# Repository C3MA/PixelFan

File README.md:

# Projektbeschreibung
In diesem Projekt wurde ein Handelsüblicher Standventilator zum Rotationsdisplay umfunktioniert.

Details und eine Präsentation dazu gibt es hier:

[C3MA Vortrag](https://www.ccc-mannheim.de/wiki/Seminar_17._M%C3%A4rz_2023)

## Aufbau
Es gibt insgesamt 3 identische LED Leisten (PCB/LED_Leiste) mit jeweils 26 HD107S LEDs.

Die LED Leisten werden dann auf der Hauptplatine (PCB/PixelFan) bestückt.

Die Hauptplatine besteht aus 2 Controllern: 

* ein STM32G071KBTX (Software unter STM_PixelFan) für die schnelle zeitkritische Ansteuerung der LEDs und der Synchronisation zur Drehung
* ein ESP32 (Software unter ESP_PixelFan) um per W-LAN eine Verbindung zur Außenwelt herzustellen

Der Ventilator öffnet ein W-LAN (SSID: PixelFan) auf dem er eine Website (unter 192.168.4.1) anzeigt. Auf der Seite können Bilder, Smileys und Text auf den Ventilator gesendet werden.

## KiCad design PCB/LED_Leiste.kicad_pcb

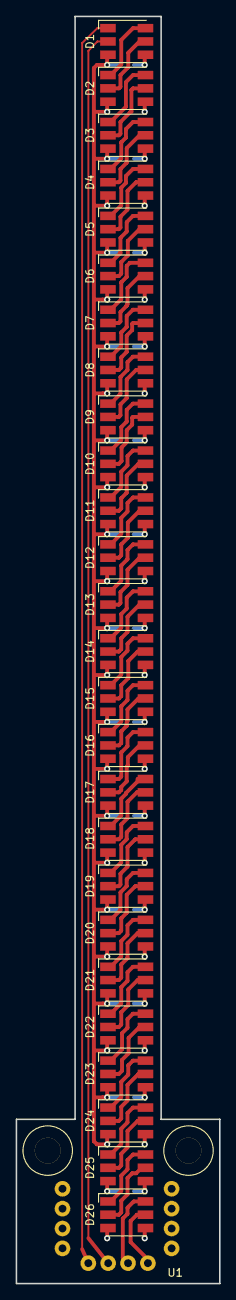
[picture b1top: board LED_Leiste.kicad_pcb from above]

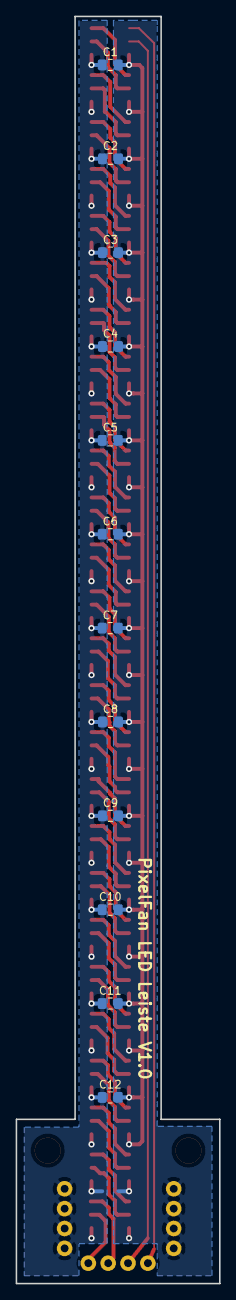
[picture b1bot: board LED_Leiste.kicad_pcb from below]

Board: 2 copper layers, 26.0 x 162.0 mm, 39 parts (12 on the bottom side), 56 nets.

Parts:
C1, C2, C3, C4, C5, C6, C7, C8, C9, C10, C11, C12: 100n; C_0805_2012Metric_Pad1.15x1.40mm_HandSolder
D1, D2, D3, D4, D5, D6, D7, D8, D9, D10, D11, D12, D13, D14, D15, D16, D17, D18, D19, D20, D21, D22, D23, D24, D25, D26: APA102; LED_RGB_5050-6
U1: Leiste; Leiste_NoOutline

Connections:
+5V: C1.1, C2.1, C3.1, C4.1, C5.1, C6.1, C7.1, C8.1, C9.1, C10.1, C11.1, C12.1, D1.4, D2.4, D3.4, D4.4, D5.4, D6.4, D7.4, D8.4, D9.4, D10.4, D11.4, D12.4, D13.4, D14.4, D15.4, D16.4, D17.4, D18.4, D19.4, D20.4, D21.4, D22.4, D23.4, D24.4, D25.4, D26.4, U1.1, U1.2, U1.3, U1.4
GND: C1.2, C2.2, C3.2, C4.2, C5.2, C6.2, C7.2, C8.2, C9.2, C10.2, C11.2, C12.2, D1.3, D2.3, D3.3, D4.3, D5.3, D6.3, D7.3, D8.3, D9.3, D10.3, D11.3, D12.3, D13.3, D14.3, D15.3, D16.3, D17.3, D18.3, D19.3, D20.3, D21.3, D22.3, D23.3, D24.3, D25.3, D26.3, U1.9, U1.10, U1.11, U1.12
unnamed: D1.1, U1.5
unnamed: D1.2, U1.6
unnamed: D1.5, D2.2
unnamed: D1.6, D2.1
unnamed: D2.5, D3.2
unnamed: D2.6, D3.1
unnamed: D3.5, D4.2
unnamed: D3.6, D4.1
unnamed: D4.5, D5.2
unnamed: D4.6, D5.1
unnamed: D5.5, D6.2
unnamed: D5.6, D6.1
unnamed: D6.5, D7.2
unnamed: D6.6, D7.1
unnamed: D7.5, D8.2
unnamed: D7.6, D8.1
unnamed: D8.5, D9.2
unnamed: D8.6, D9.1
unnamed: D9.6, D10.1
unnamed: D9.5, D10.2
unnamed: D10.5, D11.2
unnamed: D10.6, D11.1
unnamed: D11.5, D12.2
unnamed: D11.6, D12.1
unnamed: D12.5, D13.2
unnamed: D12.6, D13.1
unnamed: D13.5, D14.2
unnamed: D13.6, D14.1
unnamed: D14.5, D15.2
unnamed: D14.6, D15.1
unnamed: D15.5, D16.2
unnamed: D15.6, D16.1
unnamed: D16.5, D17.2
unnamed: D16.6, D17.1
unnamed: D17.5, D18.2
unnamed: D17.6, D18.1
unnamed: D18.5, D19.2
unnamed: D18.6, D19.1
unnamed: D19.5, D20.2
unnamed: D19.6, D20.1
unnamed: D20.5, D21.2
unnamed: D20.6, D21.1
unnamed: D21.5, D22.2
unnamed: D21.6, D22.1
unnamed: D22.5, D23.2
unnamed: D22.6, D23.1
unnamed: D23.5, D24.2
unnamed: D23.6, D24.1
unnamed: D24.5, D25.2
unnamed: D24.6, D25.1
unnamed: D25.5, D26.2
unnamed: D25.6, D26.1
unnamed: D26.5, U1.8
unnamed: D26.6, U1.7

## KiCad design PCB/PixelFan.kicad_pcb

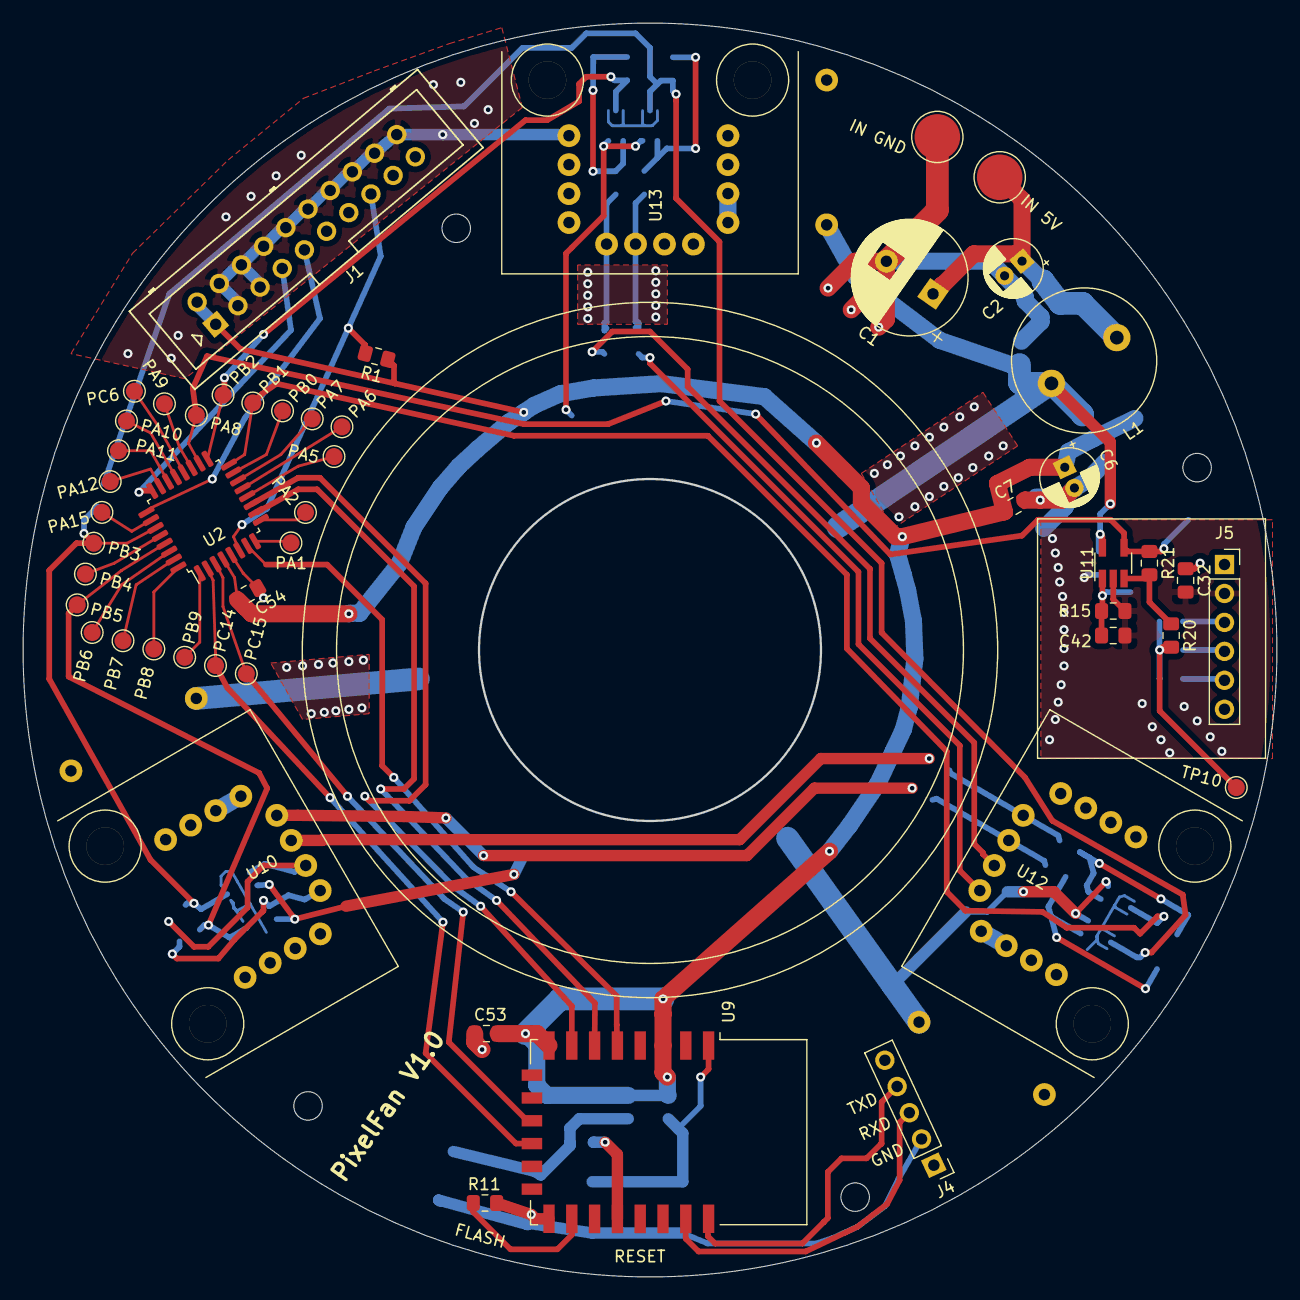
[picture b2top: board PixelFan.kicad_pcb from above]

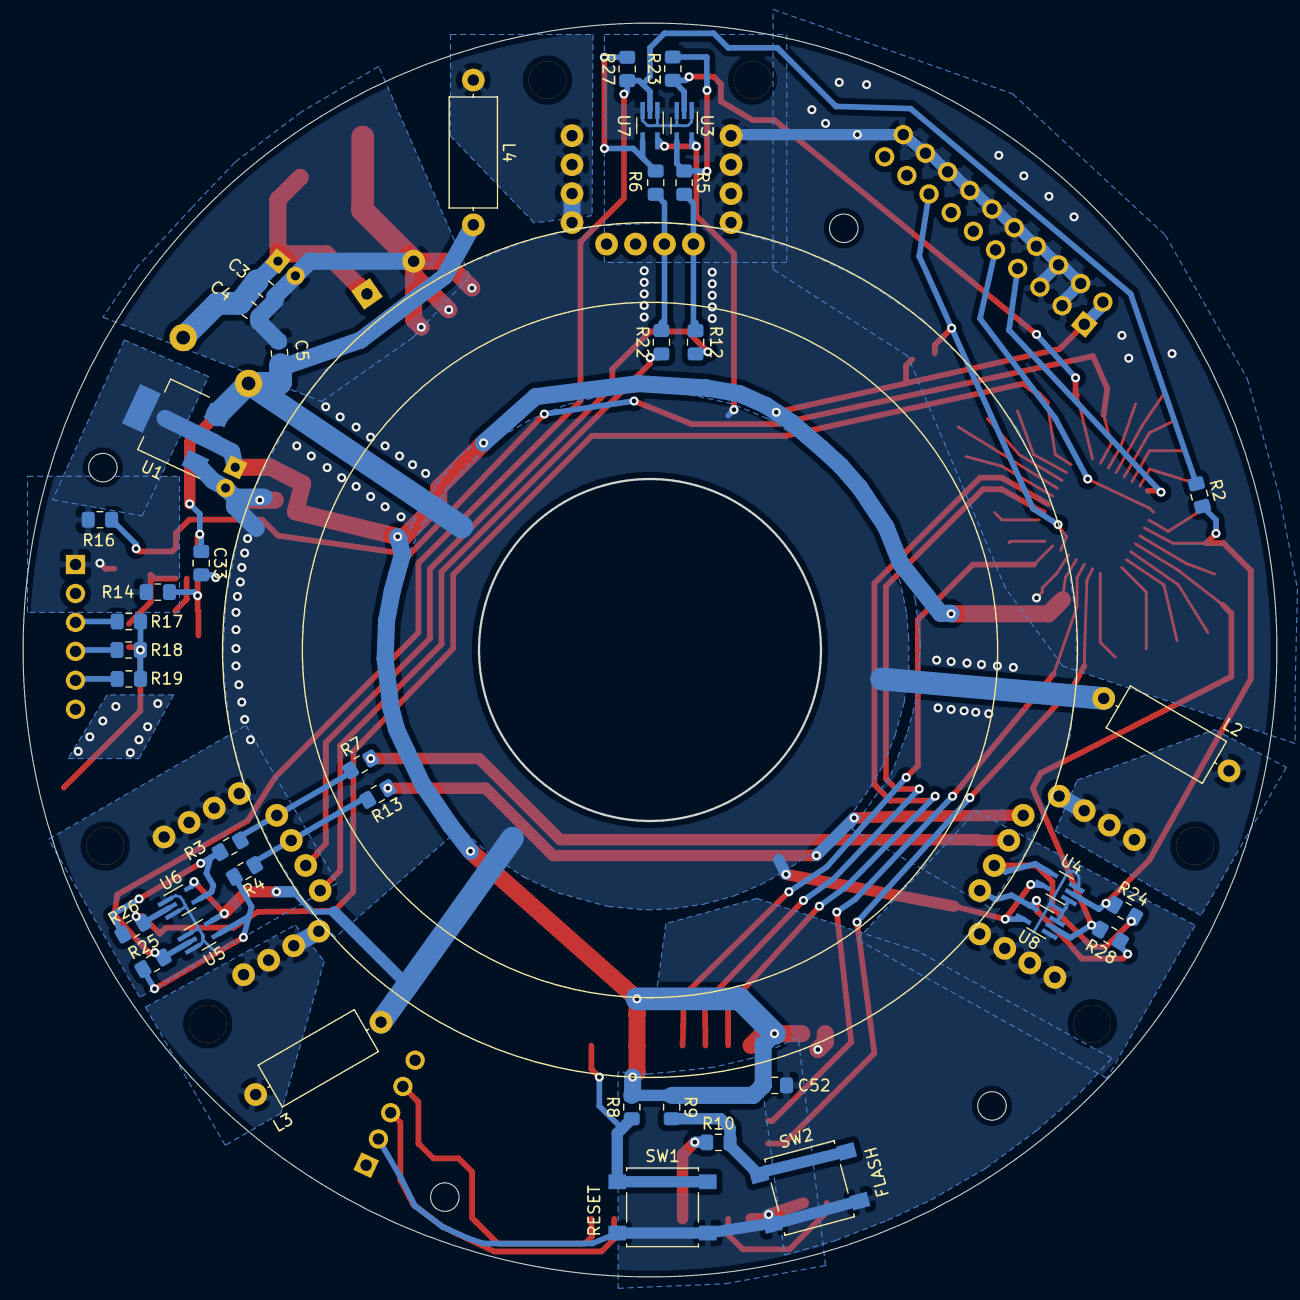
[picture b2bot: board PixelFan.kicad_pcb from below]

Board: 2 copper layers, 110.0 x 110.0 mm, 94 parts (40 on the bottom side), 64 nets.

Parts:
C1: 470µF; CP_Radial_D10.0mm_P5.00mm
C2, C6: 10u; CP_Radial_D5.0mm_P2.00mm
C3, C5, C7, C53: 470n; C_0805_2012Metric_Pad1.15x1.40mm_HandSolder
C4, C52: 10n; C_0805_2012Metric_Pad1.15x1.40mm_HandSolder
C32, C33, C42, C54: 100n; C_0805_2012Metric_Pad1.15x1.40mm_HandSolder
H1, H2, H3, H4: MountingHole; MountingHole_2.5mm
J1: Conn_02x10_Odd_Even; Multicomp_MC9A12-2034_2x10_P2.54mm_Vertical
J4: Conn_01x05_Male; PinHeader_1x05_P2.54mm_Vertical
J5: Conn_01x06_Male; PinSocket_1x06_P2.54mm_Vertical
L1: 47µH; L_Radial_D12.5mm_P7.00mm_Fastron_09HCP
L2, L3, L4: L; L_Axial_L9.5mm_D4.0mm_P12.70mm_Horizontal_Fastron_SMCC
PA1, PA2, PA5, PA6, PA7, PA8, PA9, PA10, PA11, PA12, PA15: TestPoint; TestPoint_Pad_D1.5mm
PB0, PB1, PB2, PB3, PB4, PB5, PB6, PB7, PB8, PB9: TestPoint; TestPoint_Pad_D1.5mm
PC6, PC14, PC15: TestPoint; TestPoint_Pad_D1.5mm
R1, R8, R10, R14, R16: 10k; R_0805_2012Metric_Pad1.15x1.40mm_HandSolder
R2, R3, R4, R5, R6, R7, R12, R13, R17, R18, R19, R22, R23, R24, R25, R26, R27, R28: 0; R_0805_2012Metric_Pad1.15x1.40mm_HandSolder
R9, R20: 1k; R_0805_2012Metric_Pad1.15x1.40mm_HandSolder
R11: 2k2; R_0805_2012Metric_Pad1.15x1.40mm_HandSolder
R15: 6k2; R_0805_2012Metric_Pad1.15x1.40mm_HandSolder
R21: 100k; R_0805_2012Metric_Pad1.15x1.40mm_HandSolder
SW1: Reset; SW_SPST_B3S-1000
SW2: Flash; SW_SPST_B3S-1000
TP1, TP2: TestPoint; TestPoint_Pad_D4.0mm
TP10: TestPoint; TestPoint_Pad_D1.5mm
U1: NCP1117-3.3_SOT223; SOT-223-3_TabPin2
U2: STM32G070KxTx; LQFP-32_7x7mm_P0.8mm
U3, U4, U5, U6, U7, U8: 74HCT1G125GW; SOT-353_SC-70-5_Handsoldering
U9: ESP-12F; ESP-12E
U10, U12, U13: Leiste; Leiste_WithOutline
U11: LM397; SOT-23-5_HandSoldering

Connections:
+3V3: C6.1, C7.1, C32.1, C52.1, C53.1, C54.2, J1.1, J1.2, J5.1, R1.1, R8.2, R9.1, R14.1, R16.1, U1.2, U2.4, U9.3, U9.8
+5V: C5.1, C33.1, L1.2, L2.2, L3.2, L4.2, U1.3, U3.5, U4.5, U5.5, U6.5, U7.5, U8.5, U11.5
+5VD: C1.1, C2.1, C3.1, C4.1, L1.1, TP1.1
/Beschleunigungssensor/COMP_OUT: PA8.1, R16.2, R21.1, U2.18, U11.4
/ESP8266/ESP_IO1: PC14.1, U2.2, U9.12
/ESP8266/ESP_IO2: PC15.1, U2.3, U9.11
/ESP8266/MISO: U2.10, U9.6
/ESP8266/MOSI: U2.11, U9.7
/ESP8266/SCLK: U2.7, U9.5
GND: C1.2, C2.2, C3.2, C4.2, C5.2, C6.2, C7.2, C32.2, C33.2, C42.2, C52.2, C53.2, C54.1, J1.3, J1.4, J1.5, J1.6, J1.8, J1.10, J1.12, J1.14, J1.16, J1.18, J1.20, J4.2, J5.2, R11.1, R15.2, SW1.2, SW2.2, TP2.1, U1.1, U2.5, U3.1, U3.3, U4.1, U4.3, U5.1, U5.3, U6.1, U6.3, U7.1, U7.3, U8.1, U8.3, U9.15, U10.9, U10.10, U10.11, U10.12, U11.2, U12.9, U12.10, U12.11, U12.12, U13.9, U13.10, U13.11, U13.12
unnamed: C42.1, R14.2, R15.1, U11.1
unnamed: J1.7, U2.24
unnamed: J1.9, U2.25
unnamed: J1.15, R1.2, U2.6
unnamed: J4.3, U9.21
unnamed: J4.4, U9.22
unnamed: J5.3, R17.2
unnamed: J5.4, R18.2
unnamed: J5.5, R19.2
unnamed: L2.1, U10.1, U10.2, U10.3, U10.4
unnamed: L3.1, U12.1, U12.2, U12.3, U12.4
unnamed: L4.1, U13.1, U13.2, U13.3, U13.4
unnamed: PA1.1, U2.8
unnamed: PA2.1, U2.9
unnamed: PA5.1, U2.12
unnamed: PA6.1, U2.13
unnamed: PA7.1, U2.14
unnamed: PA9.1, U2.19
unnamed: PA10.1, U2.21
unnamed: PA11.1, U2.22
unnamed: PA12.1, U2.23
unnamed: PA15.1, U2.26
unnamed: PB0.1, U2.15
unnamed: PB1.1, R26.2, U2.16, U6.2
unnamed: PB2.1, R23.1, U2.17, U3.2
unnamed: PB3.1, R2.2, R24.2, U2.27, U4.2
unnamed: PB4.1, U2.28
unnamed: PB5.1, R28.2, U2.29, U8.2
unnamed: PB6.1, U2.30
unnamed: PB7.1, U2.31
unnamed: PB8.1, U2.32
unnamed: PB9.1, U2.1
unnamed: PC6.1, U2.20
unnamed: R2.1, R25.2, R27.1, U5.2, U7.2
unnamed: R3.1, R7.2, U12.5
unnamed: R7.1, U10.7
unnamed: R8.1, SW1.1, U9.1
unnamed: R10.1, U9.18
unnamed: R9.2, R10.2, SW2.1
unnamed: R11.2, U9.16
unnamed: R12.1, U12.7
unnamed: R5.2, R12.2, U13.5
unnamed: R13.1, U10.8
unnamed: R4.1, R13.2, U12.6
unnamed: R17.1, R18.1, R19.1, R20.2, TP10.1
unnamed: R20.1, R21.2, U11.3
unnamed: R22.1, U12.8
unnamed: R6.2, R22.2, U13.6
unnamed: R5.1, R23.2, U3.4
unnamed: R24.1, U4.4, U10.6
unnamed: R4.2, R25.1, U5.4
unnamed: R3.2, R26.1, U6.4
unnamed: R6.1, R27.2, U7.4
unnamed: R28.1, U8.4, U10.5

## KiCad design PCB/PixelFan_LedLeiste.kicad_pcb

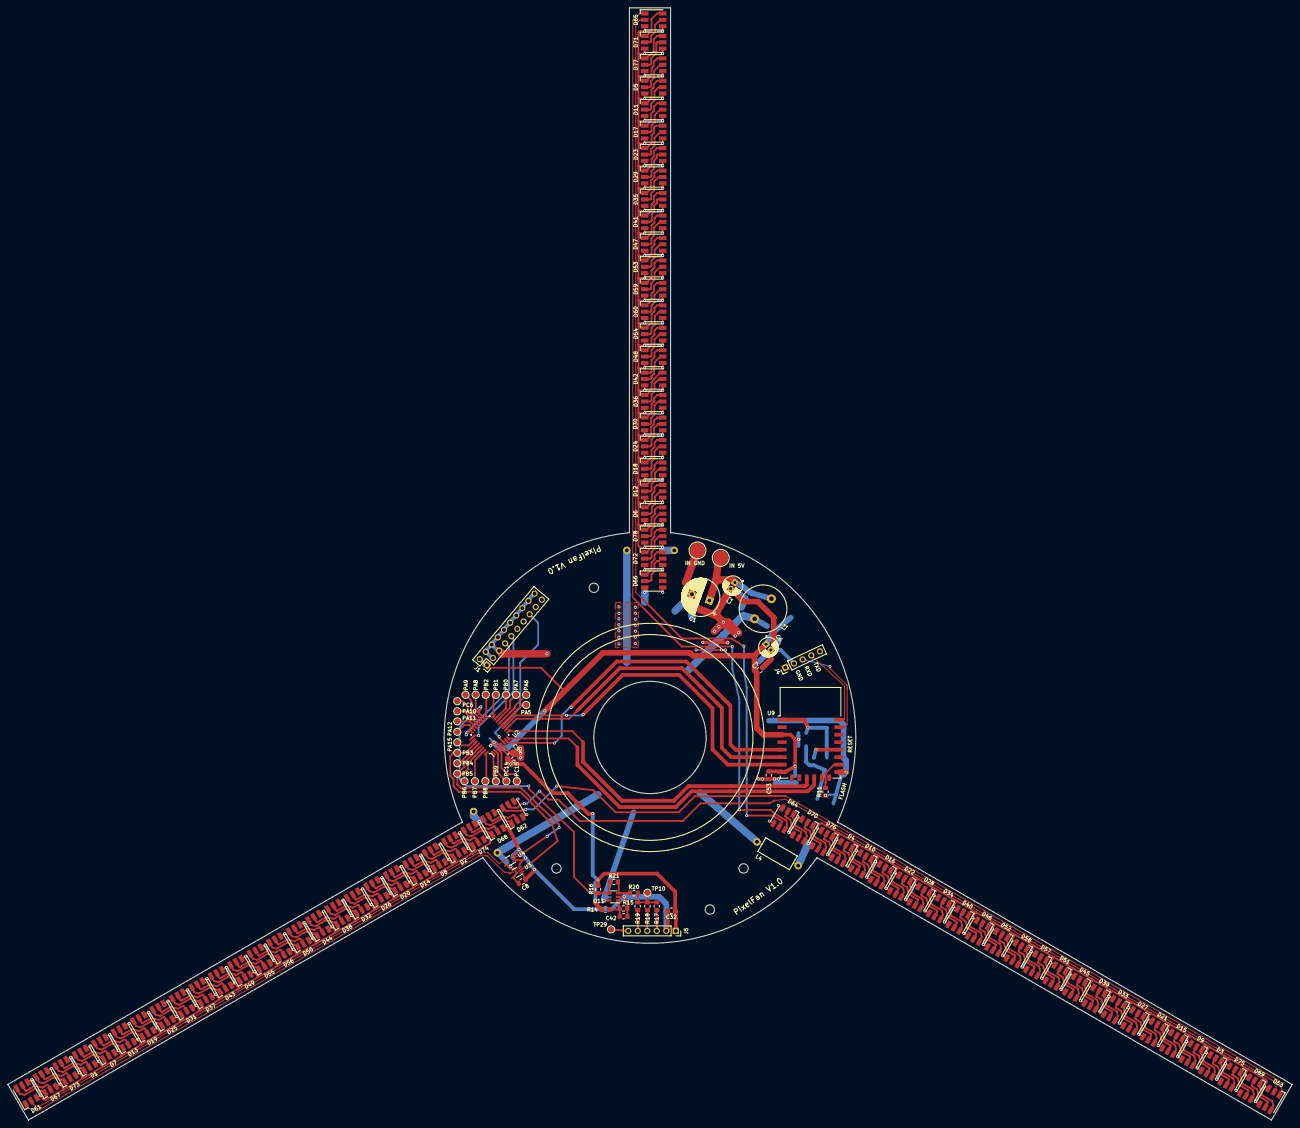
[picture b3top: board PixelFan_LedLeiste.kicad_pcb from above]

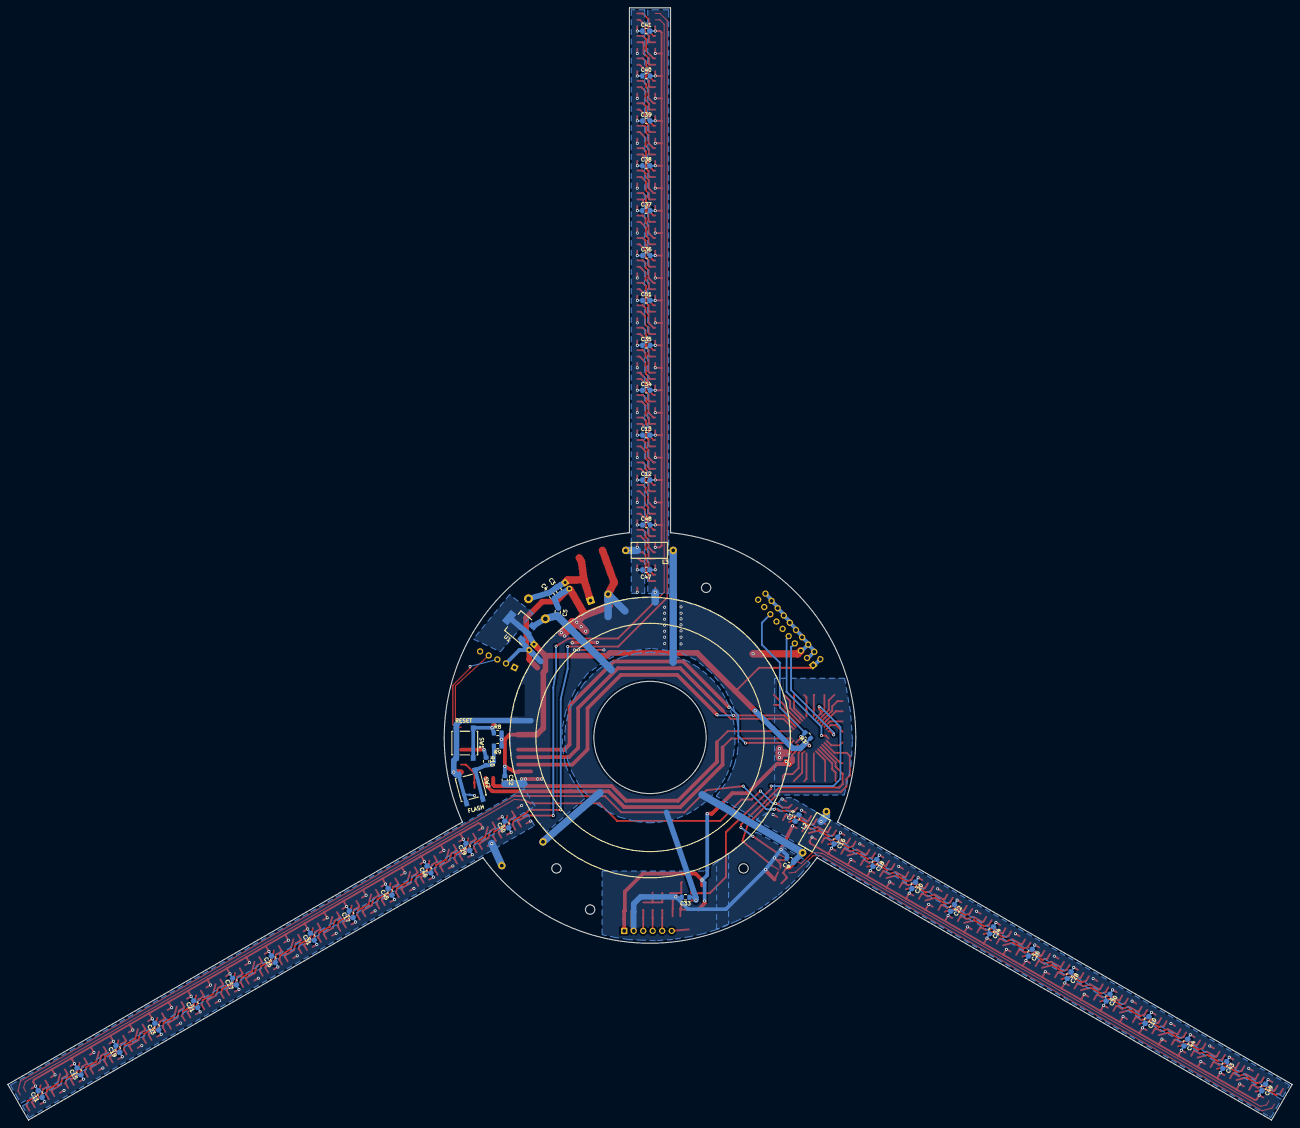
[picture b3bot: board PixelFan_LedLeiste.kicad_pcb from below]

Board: 2 copper layers, 343.2 x 297.3 mm, 190 parts (54 on the bottom side), 206 nets.

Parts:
C1: 470µF; CP_Radial_D10.0mm_P5.00mm
C2, C6: 10u; CP_Radial_D5.0mm_P2.00mm
C3, C5, C7, C53: 470n; C_0805_2012Metric_Pad1.15x1.40mm_HandSolder
C4, C52: 10n; C_0805_2012Metric_Pad1.15x1.40mm_HandSolder
C8, C9, C10, C11, C12, C13, C14, C15, C16, C17, C18, C19, C20, C21, C22, C23, C24, C25, C26, C27, C28, C29, C30, C31, C32, C33, C34, C35, C36, C37, C38, C39, C40, C41, C42, C43, C44, C45, C46, C47, C48, C49, C50, C51, C54: 100n; C_0805_2012Metric_Pad1.15x1.40mm_HandSolder
D1, D2, D3, D4, D5, D6, D7, D8, D9, D10, D11, D12, D13, D14, D15, D16, D17, D18, D19, D20, D21, D22, D23, D24, D25, D26, D27, D28, D29, D30, D31, D32, D33, D34, D35, D36, D37, D38, D39, D40, D41, D42, D43, D44, D45, D46, D47, D48, D49, D50, D51, D52, D53, D54, D55, D56, D57, D58, D59, D60, D61, D62, D63, D64, D65, D66, D67, D68, D69, D70, D71, D72, D73, D74, D75, D76, D77, D78: APA102; LED_RGB_5050-6
H1, H2, H3, H4: MountingHole; MountingHole_2.5mm
J1: Conn_02x10_Odd_Even; PinHeader_2x10_P2.54mm_Vertical
J4: Conn_01x05_Male; PinHeader_1x05_P2.54mm_Vertical
J5: Conn_01x06_Male; PinSocket_1x06_P2.54mm_Vertical
L1: 47µH; L_Radial_D12.5mm_P7.00mm_Fastron_09HCP
L2, L3, L4: 1u; L_Axial_L9.5mm_D4.0mm_P12.70mm_Horizontal_Fastron_SMCC
PA5, PA6, PA7, PA8, PA9, PA10, PA11, PA12, PA15: TestPoint; TestPoint_Pad_D1.5mm
PB0, PB1, PB2, PB3, PB4, PB5, PB6, PB7, PB8, PB9: TestPoint; TestPoint_Pad_D1.5mm
PC6, PC14, PC15: TestPoint; TestPoint_Pad_D1.5mm
R1, R8, R10, R14, R15, R16: 10k; R_0805_2012Metric_Pad1.15x1.40mm_HandSolder
R9, R20: 1k; R_0805_2012Metric_Pad1.15x1.40mm_HandSolder
R11: 2k2; R_0805_2012Metric_Pad1.15x1.40mm_HandSolder
R17, R18, R19: 0; R_0805_2012Metric_Pad1.15x1.40mm_HandSolder
R21: 100k; R_0805_2012Metric_Pad1.15x1.40mm_HandSolder
SW1: Reset; SW_SPST_B3S-1000
SW2: Flash; SW_SPST_B3S-1000
TP1, TP2: TestPoint; TestPoint_Pad_D4.0mm
TP10, TP29: TestPoint; TestPoint_Pad_D1.5mm
U1: NCP1117-3.3_SOT223; SOT-223-3_TabPin2
U2: STM32G070KxTx; LQFP-32_7x7mm_P0.8mm
U3, U4: 74HCT1G125GW; SOT-353_SC-70-5_Handsoldering
U9: ESP-12F; ESP-12E
U11: LM397; SOT-23-5_HandSoldering

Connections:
+3V3: C6.1, C7.1, C32.1, C52.1, C53.1, C54.2, J1.1, J1.2, J5.1, R1.1, R8.2, R9.1, R14.1, R16.1, U1.2, U2.4, U9.3, U9.8
+5V: C5.1, C8.1, C9.2, C33.1, L1.2, L2.1, L3.1, L4.1, U1.3, U3.5, U4.5, U11.5
+5VD: C1.1, C2.1, C3.1, C4.1, L1.1, TP1.1
/Beschleunigungssensor/COMP_OUT: PA8.1, R16.2, R21.1, U2.18, U11.4
/ESP8266/ESP_IO1: U2.8, U9.12
/ESP8266/ESP_IO2: U2.9, U9.11
/ESP8266/MISO: U2.10, U9.6
/ESP8266/MOSI: U2.11, U9.7
/ESP8266/SCLK: U2.7, U9.5
/LEDs/CLK: PB3.1, U2.27, U3.2
/LEDs/DATA: PB5.1, U2.29, U4.2
/LEDs/VCC_LINE1: C10.1, C14.1, C16.1, C18.1, C20.1, C22.1, C24.1, C26.1, C28.1, C30.1, C43.1, C44.1, C49.1, D1.4, D2.4, D7.4, D8.4, D13.4, D14.4, D19.4, D20.4, D25.4, D26.4, D31.4, D32.4, D37.4, D38.4, D43.4, D44.4, D49.4, D50.4, D55.4, D56.4, D61.4, D62.4, D67.4, D68.4, D73.4, D74.4, L2.2
/LEDs/VCC_LINE2: C11.1, C15.1, C17.1, C19.1, C21.1, C23.1, C25.1, C27.1, C29.1, C31.1, C45.1, C46.1, C50.1, D3.4, D4.4, D9.4, D10.4, D15.4, D16.4, D21.4, D22.4, D27.4, D28.4, D33.4, D34.4, D39.4, D40.4, D45.4, D46.4, D51.4, D52.4, D57.4, D58.4, D63.4, D64.4, D69.4, D70.4, D75.4, D76.4, L4.2
/LEDs/VCC_LINE3: C12.1, C13.1, C34.1, C35.1, C36.1, C37.1, C38.1, C39.1, C40.1, C41.1, C47.1, C48.1, C51.1, D5.4, D6.4, D11.4, D12.4, D17.4, D18.4, D23.4, D24.4, D29.4, D30.4, D35.4, D36.4, D41.4, D42.4, D47.4, D48.4, D53.4, D54.4, D59.4, D60.4, D65.4, D66.4, D71.4, D72.4, D77.4, D78.4, L3.2
GND: C1.2, C2.2, C3.2, C4.2, C5.2, C6.2, C7.2, C8.2, C9.1, C10.2, C11.2, C12.2, C13.2, C14.2, C15.2, C16.2, C17.2, C18.2, C19.2, C20.2, C21.2, C22.2, C23.2, C24.2, C25.2, C26.2, C27.2, C28.2, C29.2, C30.2, C31.2, C32.2, C33.2, C34.2, C35.2, C36.2, C37.2, C38.2, C39.2, C40.2, C41.2, C42.2, C43.2, C44.2, C45.2, C46.2, C47.2, C48.2, C49.2, C50.2, C51.2, C52.2, C53.2, C54.1, D1.3, D2.3, D3.3, D4.3, D5.3, D6.3, D7.3, D8.3, D9.3, D10.3, D11.3, D12.3, D13.3, D14.3, D15.3, D16.3, D17.3, D18.3, D19.3, D20.3, D21.3, D22.3, D23.3, D24.3, D25.3, D26.3, D27.3, D28.3, D29.3, D30.3, D31.3, D32.3, D33.3, D34.3, D35.3, D36.3, D37.3, D38.3, D39.3, D40.3, D41.3, D42.3, D43.3, D44.3, D45.3, D46.3, D47.3, D48.3, D49.3, D50.3, D51.3, D52.3, D53.3, D54.3, D55.3, D56.3, D57.3, D58.3, D59.3, D60.3, D61.3, D62.3, D63.3, D64.3, D65.3, D66.3, D67.3, D68.3, D69.3, D70.3, D71.3, D72.3, D73.3, D74.3, D75.3, D76.3, D77.3, D78.3, J1.3, J1.4, J1.5, J1.6, J1.8, J1.10, J1.12, J1.14, J1.16, J1.18, J1.20, J4.2, J5.2, R11.1, R15.2, SW1.2, SW2.2, TP2.1, U1.1, U2.5, U3.1, U3.3, U4.1, U4.3, U9.15, U11.2
unnamed: C42.1, R14.2, R15.1, U11.1
unnamed: D1.1, D73.6
unnamed: D1.2, D73.5
unnamed: D1.5, D7.2
unnamed: D1.6, D7.1
unnamed: D2.1, D8.6
unnamed: D2.2, D8.5
unnamed: D2.5, D74.2
unnamed: D2.6, D74.1
unnamed: D3.1, D75.6
unnamed: D3.2, D75.5
unnamed: D3.5, D9.2
unnamed: D3.6, D9.1
unnamed: D4.5, D76.2
unnamed: D4.6, D76.1
unnamed: D5.1, D77.6
unnamed: D5.2, D77.5
unnamed: D6.5, D78.2
unnamed: D6.6, D78.1
unnamed: D10.1, D16.6
unnamed: D10.2, D16.5
unnamed: D4.2, D10.5
unnamed: D4.1, D10.6
unnamed: D5.6, D11.1
unnamed: D5.5, D11.2
unnamed: D11.5, D17.2
unnamed: D11.6, D17.1
unnamed: D12.1, D18.6
unnamed: D12.2, D18.5
unnamed: D6.2, D12.5
unnamed: D6.1, D12.6
unnamed: D7.6, D13.1
unnamed: D7.5, D13.2
unnamed: D13.5, D19.2
unnamed: D13.6, D19.1
unnamed: D14.1, D20.6
unnamed: D14.2, D20.5
unnamed: D8.2, D14.5
unnamed: D8.1, D14.6
unnamed: D9.6, D15.1
unnamed: D9.5, D15.2
unnamed: D15.5, D21.2
unnamed: D15.6, D21.1
unnamed: D16.1, D22.6
unnamed: D16.2, D22.5
unnamed: D17.5, D23.2
unnamed: D17.6, D23.1
unnamed: D18.1, D24.6
unnamed: D18.2, D24.5
unnamed: D19.5, D25.2
unnamed: D19.6, D25.1
unnamed: D20.1, D26.6
unnamed: D20.2, D26.5
unnamed: D21.5, D27.2
unnamed: D21.6, D27.1
unnamed: D22.1, D28.6
unnamed: D22.2, D28.5
unnamed: D23.5, D29.2
unnamed: D23.6, D29.1
unnamed: D24.1, D30.6
unnamed: D24.2, D30.5
unnamed: D25.5, D31.2
unnamed: D25.6, D31.1
unnamed: D26.1, D32.6
unnamed: D26.2, D32.5
unnamed: D27.5, D33.2
unnamed: D27.6, D33.1
unnamed: D28.1, D34.6
unnamed: D28.2, D34.5
unnamed: D29.5, D35.2
unnamed: D29.6, D35.1
unnamed: D30.1, D36.6
unnamed: D30.2, D36.5
unnamed: D31.5, D37.2
unnamed: D31.6, D37.1
unnamed: D32.1, D38.6
unnamed: D32.2, D38.5
unnamed: D33.5, D39.2
unnamed: D33.6, D39.1
unnamed: D34.1, D40.6
unnamed: D34.2, D40.5
unnamed: D35.5, D41.2
unnamed: D35.6, D41.1
unnamed: D36.1, D42.6
unnamed: D36.2, D42.5
unnamed: D37.5, D43.2
unnamed: D37.6, D43.1
unnamed: D38.1, D44.6
unnamed: D38.2, D44.5
unnamed: D39.5, D45.2
unnamed: D39.6, D45.1
unnamed: D40.1, D46.6
unnamed: D40.2, D46.5
unnamed: D41.5, D47.2
unnamed: D41.6, D47.1
unnamed: D42.1, D48.6
unnamed: D42.2, D48.5
unnamed: D43.5, D49.2
unnamed: D43.6, D49.1
unnamed: D44.1, D50.6
unnamed: D44.2, D50.5
unnamed: D45.5, D51.2
unnamed: D45.6, D51.1
unnamed: D46.1, D52.6
unnamed: D46.2, D52.5
unnamed: D47.5, D53.2
unnamed: D47.6, D53.1
unnamed: D48.1, D54.6
unnamed: D48.2, D54.5
unnamed: D49.5, D55.2
unnamed: D49.6, D55.1
unnamed: D50.1, D56.6
unnamed: D50.2, D56.5
unnamed: D51.5, D57.2
unnamed: D51.6, D57.1
unnamed: D52.1, D58.6
unnamed: D52.2, D58.5
unnamed: D53.5, D59.2
unnamed: D53.6, D59.1
unnamed: D54.1, D60.6
unnamed: D54.2, D60.5
unnamed: D55.5, D56.2
unnamed: D55.6, D56.1
unnamed: D57.5, D58.2
unnamed: D57.6, D58.1
unnamed: D59.5, D60.2
unnamed: D59.6, D60.1
unnamed: D61.1, U3.4
unnamed: D61.2, U4.4
unnamed: D61.5, D67.2
unnamed: D61.6, D67.1
unnamed: D62.1, D68.6
unnamed: D62.2, D68.5
unnamed: D62.5, D63.2
unnamed: D62.6, D63.1
unnamed: D63.5, D69.2
unnamed: D63.6, D69.1
unnamed: D64.1, D70.6
unnamed: D64.2, D70.5
unnamed: D64.5, D65.2
unnamed: D64.6, D65.1
unnamed: D65.5, D71.2
unnamed: D65.6, D71.1
unnamed: D66.1, D72.6
unnamed: D66.2, D72.5
unnamed: D67.5, D73.2
unnamed: D67.6, D73.1
unnamed: D68.1, D74.6
unnamed: D68.2, D74.5
unnamed: D69.5, D75.2
unnamed: D69.6, D75.1
unnamed: D70.1, D76.6
unnamed: D70.2, D76.5
unnamed: D71.5, D77.2
unnamed: D71.6, D77.1
unnamed: D72.1, D78.6
unnamed: D72.2, D78.5
unnamed: J1.7, U2.24
unnamed: J1.9, U2.25
unnamed: J1.15, R1.2, U2.6
unnamed: J4.3, U9.21
unnamed: J4.4, U9.22
unnamed: J5.3, R17.2
unnamed: J5.4, R18.2
unnamed: J5.5, R19.2
unnamed: J5.6, TP29.1
unnamed: PA5.1, U2.12
unnamed: PA6.1, U2.13
unnamed: PA7.1, U2.14
unnamed: PA9.1, U2.19
unnamed: PA10.1, U2.21
unnamed: PA11.1, U2.22
unnamed: PA12.1, U2.23
unnamed: PA15.1, U2.26
unnamed: PB0.1, U2.15
unnamed: PB1.1, U2.16
unnamed: PB2.1, U2.17
unnamed: PB4.1, U2.28
unnamed: PB6.1, U2.30
unnamed: PB7.1, U2.31
unnamed: PB8.1, U2.32
unnamed: PB9.1, U2.1
unnamed: PC6.1, U2.20
unnamed: PC14.1, U2.2
unnamed: PC15.1, U2.3
unnamed: R8.1, SW1.1, U9.1
unnamed: R10.1, U9.18
unnamed: R9.2, R10.2, SW2.1
unnamed: R11.2, U9.16
unnamed: R17.1, R18.1, R19.1, R20.2, TP10.1
unnamed: R20.1, R21.2, U11.3

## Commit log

2023-01-25 First check in
2023-01-25 First checkin
2023-01-26 arduino install script for action
2023-01-26 ESP core install script for action
2023-01-26 Arduino Build with ESP core
2023-01-26 Platform source-path ergänzt
2023-01-26 WebSocketServer Bibliothek ergänzt
2023-01-26 Library name korrigiert
2023-01-26 Update README.md
    Statusbadge für ESP Projekt ergänzt
2023-02-15 Bild rotiert, sodass es wieder gerade steht.
2023-02-16 Check In PCB Files
